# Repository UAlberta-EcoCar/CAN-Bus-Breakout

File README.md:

# CAN-Bus-Breakout
Breakout board for mcp2515 CAN bus controllor.

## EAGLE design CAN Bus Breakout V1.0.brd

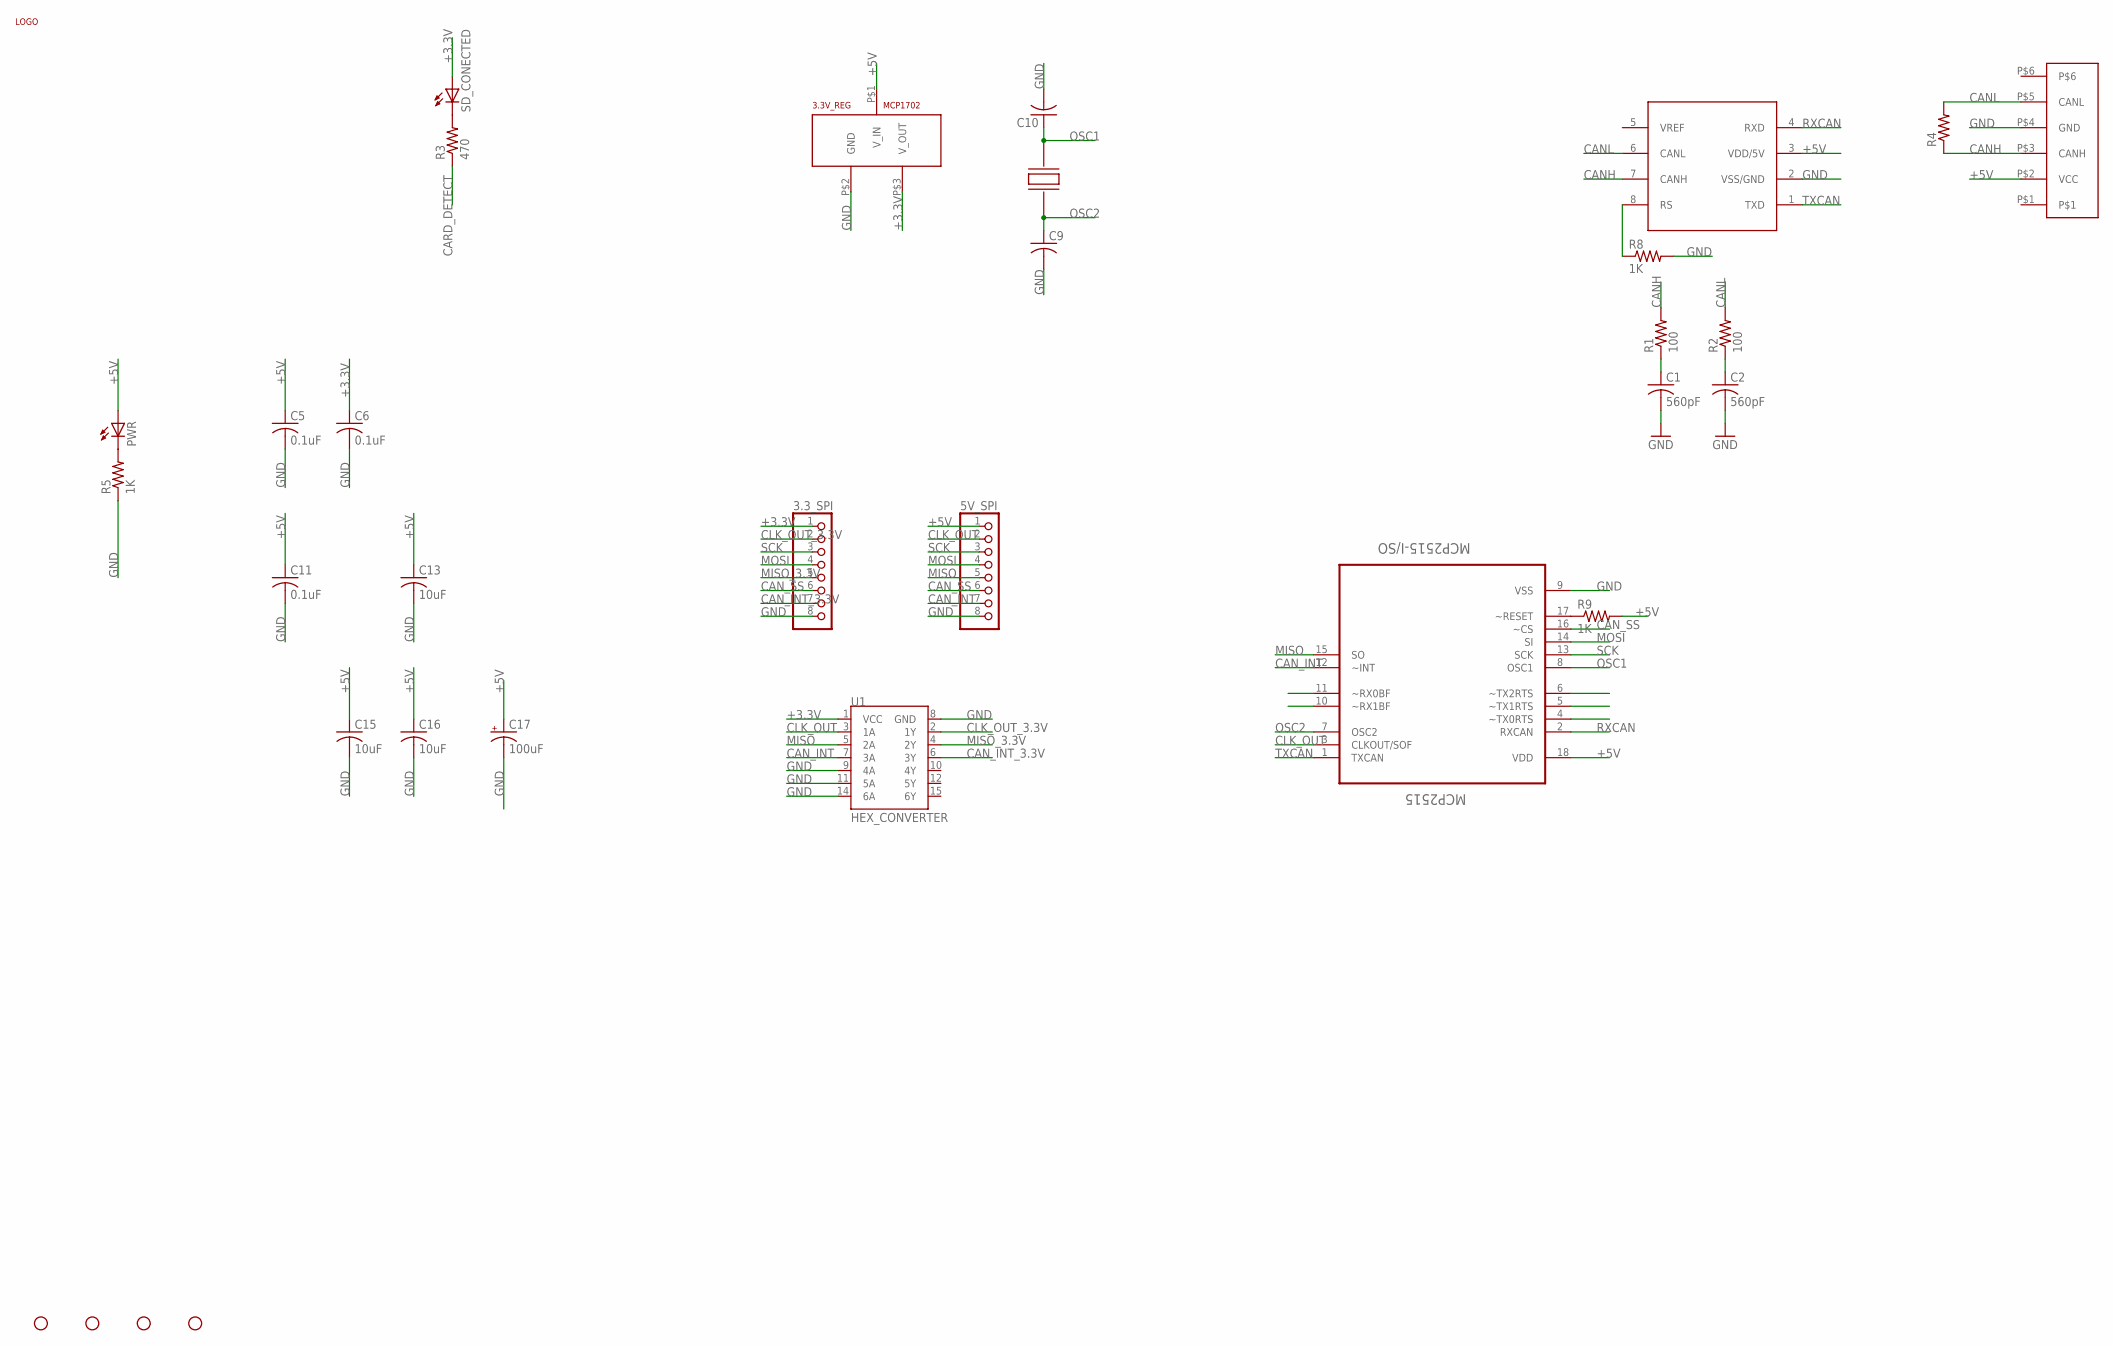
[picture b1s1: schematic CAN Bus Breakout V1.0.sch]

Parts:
3.3V_REG: MCP1702; SOT-23A
3.3_SPI, 5V_SPI: PINHD-1X8CLEANBIG; 1X08-CLEANBIG
C1, C2: 560pF; C0805
C5, C6, C11: 0.1uF; C0805
C9, C10: C-USC0805; C0805
C13, C15, C16: 10uF; C0805
C17: 100uF; PANASONIC_D
MCP2515: MCP2515-I/SO; SOIC127P1034X264-18N
PWR: LED1206; LED-1206
R1, R2: 100; M0805
R3: 470; M0805
R4: R-US_M0805; M0805
R5, R8, R9: 1K; M0805
SD_CONECTED: LED1206; LED-1206
STANDOFF1, STANDOFF2, STANDOFF3, STANDOFF4: STAND-OFF
U1: HEX_CONVERTER; SO016
U$1: CAN_6P6C
U$2: MCP2551DIP; DIP8
U$3: LOGO
U$19: CRYSTAL; 7A_CRYSTAL

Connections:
+3.3V: 3.3V_REG.P$3 (V_OUT), 3.3_SPI.1, C6.1, SD_CONECTED.A, U1.1 (VCC)
+5V: 3.3V_REG.P$1 (V_IN), 5V_SPI.1, C5.1, C11.1, C13.1, C15.1, C16.1, C17.+, MCP2515.18 (VDD), PWR.A, R9.2, U$1.P$2 (VCC), U$2.3 (VDD/5V)
CANH: R1.2, R4.1, U$1.P$3 (CANH), U$2.7 (CANH)
CANL: R2.2, R4.2, U$1.P$5 (CANL), U$2.6 (CANL)
CAN_INT: 5V_SPI.7, MCP2515.12 (~INT), U1.7 (3A)
CAN_INT_3.3V: 3.3_SPI.7, U1.6 (3Y)
CAN_SS: 3.3_SPI.6, 5V_SPI.6, MCP2515.16 (~CS)
CARD_DETECT: R3.1
CLK_OUT: 5V_SPI.2, MCP2515.3 (CLKOUT/SOF), U1.3 (1A)
CLK_OUT_3.3V: 3.3_SPI.2, U1.2 (1Y)
GND: 3.3V_REG.P$2 (GND), 3.3_SPI.8, 5V_SPI.8, C1.2, C2.2, C5.2, C6.2, C9.2, C10.2, C11.2, C13.2, C15.2, C16.2, C17.-, MCP2515.9 (VSS), R5.1, R8.2, U1.8 (GND), U1.9 (4A), U1.11 (5A), U1.14 (6A), U$1.P$4 (GND), U$2.2 (VSS/GND)
MISO: 5V_SPI.5, MCP2515.15 (SO), U1.5 (2A)
MISO_3.3V: 3.3_SPI.5, U1.4 (2Y)
MOSI: 3.3_SPI.4, 5V_SPI.4, MCP2515.14 (SI)
unnamed: R3.2, SD_CONECTED.C
unnamed: R8.1, U$2.8 (RS)
unnamed: MCP2515.17 (~RESET), R9.1
unnamed: PWR.C, R5.2
unnamed: C1.1, R1.1
unnamed: C2.1, R2.1
OSC1: C10.1, MCP2515.8 (OSC1), U$19.P$2
OSC2: C9.1, MCP2515.7 (OSC2), U$19.P$1
RXCAN: MCP2515.2 (RXCAN), U$2.4 (RXD)
SCK: 3.3_SPI.3, 5V_SPI.3, MCP2515.13 (SCK)
TXCAN: MCP2515.1 (TXCAN), U$2.1 (TXD)

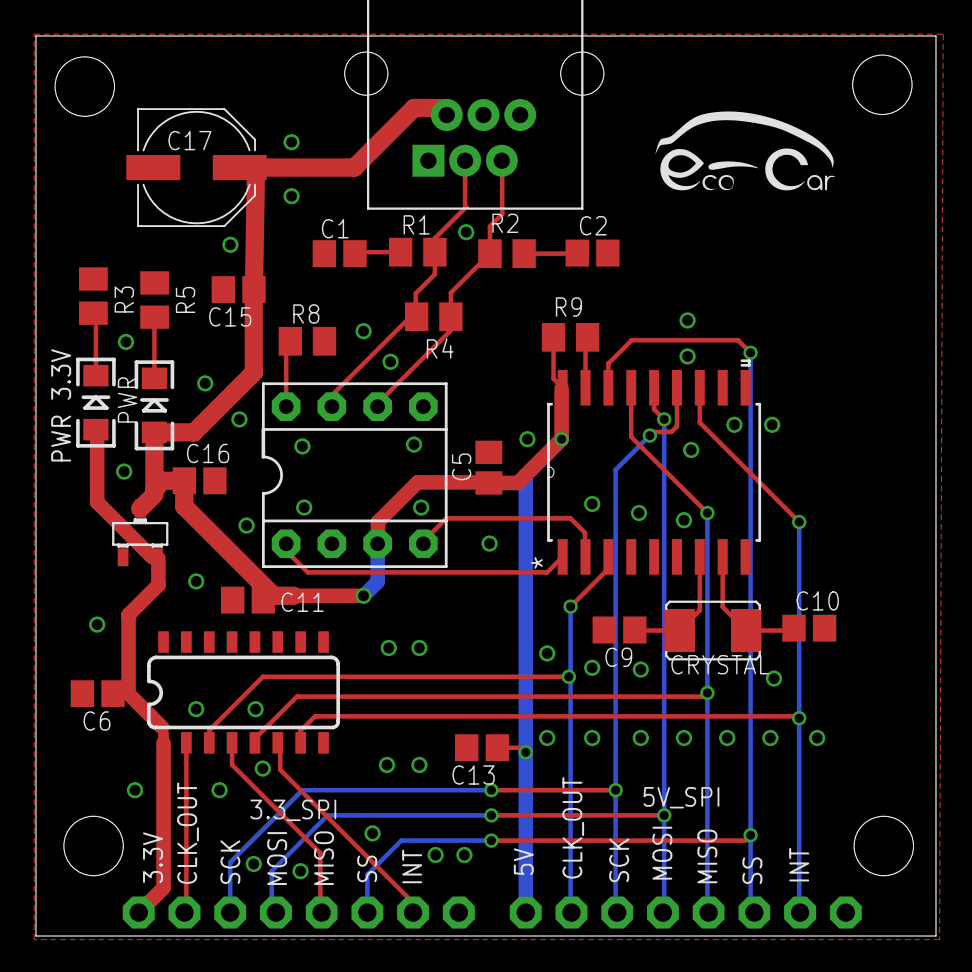
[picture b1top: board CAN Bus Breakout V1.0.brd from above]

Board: 2 copper layers, 50.0 x 50.0 mm, 33 parts (0 on the bottom side), 24 nets.

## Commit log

2016-02-14 Board Layout done
2016-02-15 Complete

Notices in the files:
parts and their libraries:
SparkFun-Capacitors: Licensing: Creative Commons ShareAlike 4.0 International - https://creativecommons.org/licenses/by-sa/4.0
